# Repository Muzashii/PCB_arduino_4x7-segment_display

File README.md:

# PCB_arduino_4x7-segment_display
PCB of a module for arduino, with 4 LEDs of 7 segments for counting

# Imagens

Assembly on TinkerCad : 

Schematic of the project : 

Top layer of 3D PCB : 

Detail of the use of each pin entry : 

## Installation

##### Use KiCad to open the project file

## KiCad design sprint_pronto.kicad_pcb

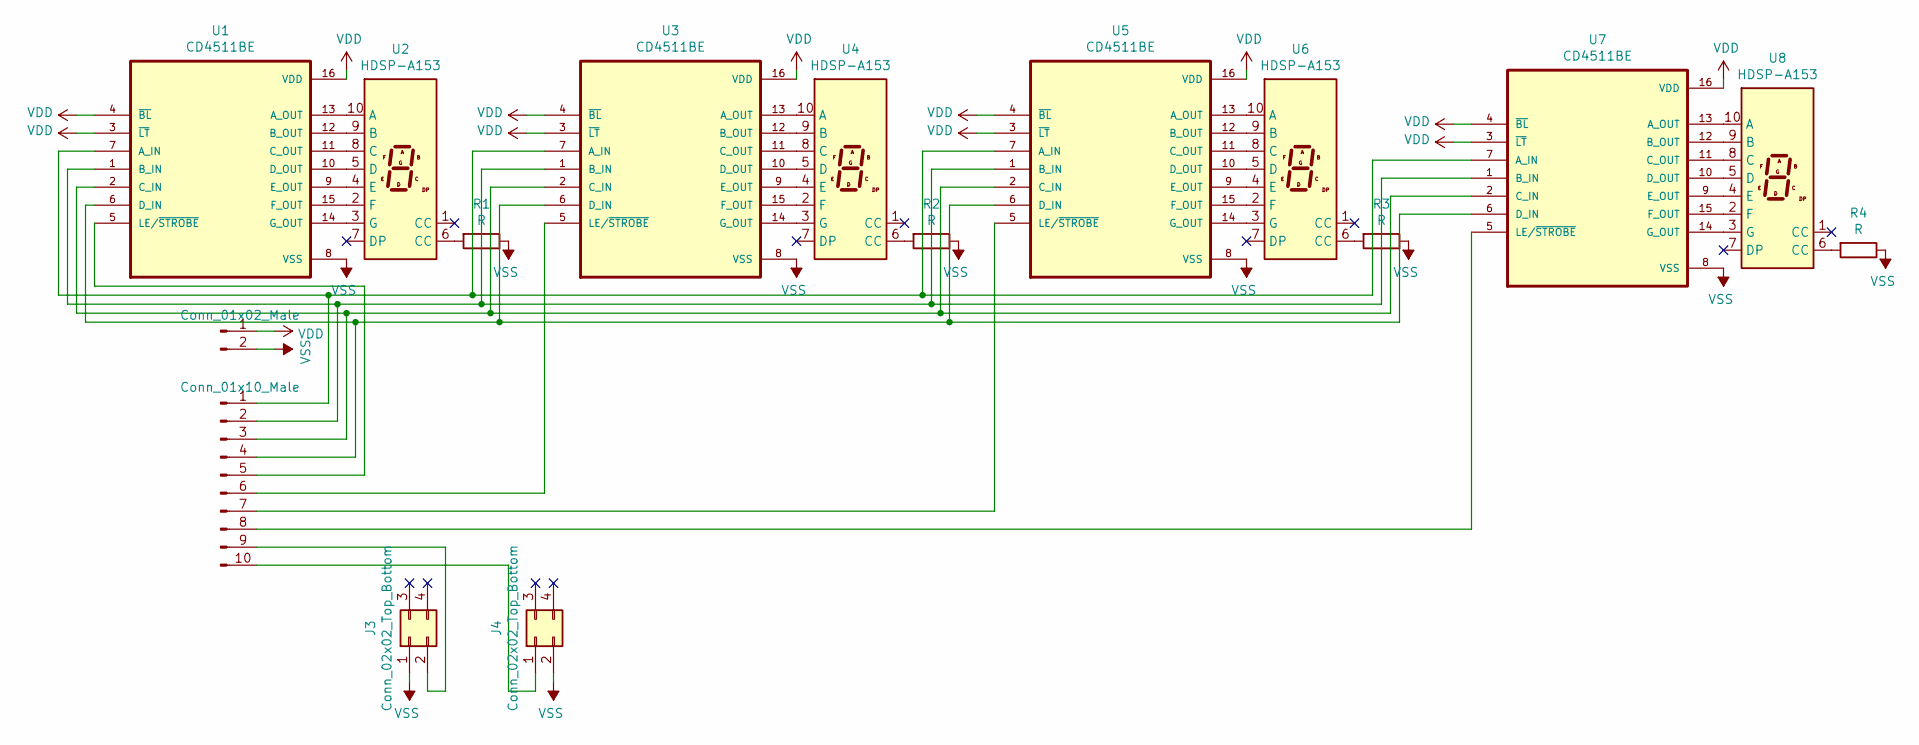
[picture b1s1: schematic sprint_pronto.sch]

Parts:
J1: Conn_01x02_Male; PinHeader_1x02_P2.54mm_Vertical
J2: Conn_01x10_Male; PinHeader_1x10_P2.54mm_Vertical
J3, J4: Conn_02x02_Top_Bottom; SW_PUSH_6mm_H5mm
R1, R2, R3, R4: R; R_Axial_DIN0207_L6.3mm_D2.5mm_P10.16mm_Horizontal
U1, U3, U5, U7: CD4511BE; DIP794W45P254L1969H508Q16
U2, U4, U6, U8: HDSP-A153; HDSP-A151

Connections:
unnamed: J2.1, U1.7 (A_IN), U3.7 (A_IN), U5.7 (A_IN), U7.7 (A_IN)
unnamed: J2.2, U1.1 (B_IN), U3.1 (B_IN), U5.1 (B_IN), U7.1 (B_IN)
unnamed: J2.3, U1.2 (C_IN), U3.2 (C_IN), U5.2 (C_IN), U7.2 (C_IN)
unnamed: J2.4, U1.6 (D_IN), U3.6 (D_IN), U5.6 (D_IN), U7.6 (D_IN)
unnamed: J2.5, U1.5 (LE/~STROBE)
unnamed: J2.6, U3.5 (LE/~STROBE)
unnamed: J2.7, U5.5 (LE/~STROBE)
unnamed: J2.8, U7.5 (LE/~STROBE)
unnamed: J2.9, J3.2
unnamed: J2.10, J4.1
unnamed: R1.2, U2.6 (CC)
unnamed: R2.2, U4.6 (CC)
unnamed: R3.2, U6.6 (CC)
unnamed: R4.2, U8.6 (CC)
unnamed: U1.9 (E_OUT), U2.4 (E)
unnamed: U1.10 (D_OUT), U2.5 (D)
unnamed: U1.11 (C_OUT), U2.8 (C)
unnamed: U1.12 (B_OUT), U2.9 (B)
unnamed: U1.13 (A_OUT), U2.10 (A)
unnamed: U1.14 (G_OUT), U2.3 (G)
unnamed: U1.15 (F_OUT), U2.2 (F)
unnamed: U3.9 (E_OUT), U4.4 (E)
unnamed: U3.10 (D_OUT), U4.5 (D)
unnamed: U3.11 (C_OUT), U4.8 (C)
unnamed: U3.12 (B_OUT), U4.9 (B)
unnamed: U3.13 (A_OUT), U4.10 (A)
unnamed: U3.14 (G_OUT), U4.3 (G)
unnamed: U3.15 (F_OUT), U4.2 (F)
unnamed: U5.9 (E_OUT), U6.4 (E)
unnamed: U5.10 (D_OUT), U6.5 (D)
unnamed: U5.11 (C_OUT), U6.8 (C)
unnamed: U5.12 (B_OUT), U6.9 (B)
unnamed: U5.13 (A_OUT), U6.10 (A)
unnamed: U5.14 (G_OUT), U6.3 (G)
unnamed: U5.15 (F_OUT), U6.2 (F)
unnamed: U7.9 (E_OUT), U8.4 (E)
unnamed: U7.10 (D_OUT), U8.5 (D)
unnamed: U7.11 (C_OUT), U8.8 (C)
unnamed: U7.12 (B_OUT), U8.9 (B)
unnamed: U7.13 (A_OUT), U8.10 (A)
unnamed: U7.14 (G_OUT), U8.3 (G)
unnamed: U7.15 (F_OUT), U8.2 (F)
VDD: J1.1, U1.3 (~LT), U1.4 (~BL), U1.16 (VDD), U3.3 (~LT), U3.4 (~BL), U3.16 (VDD), U5.3 (~LT), U5.4 (~BL), U5.16 (VDD), U7.3 (~LT), U7.4 (~BL), U7.16 (VDD)
VSS: J1.2, J3.1, J4.2, R1.1, R2.1, R3.1, R4.1, U1.8 (VSS), U3.8 (VSS), U5.8 (VSS), U7.8 (VSS)

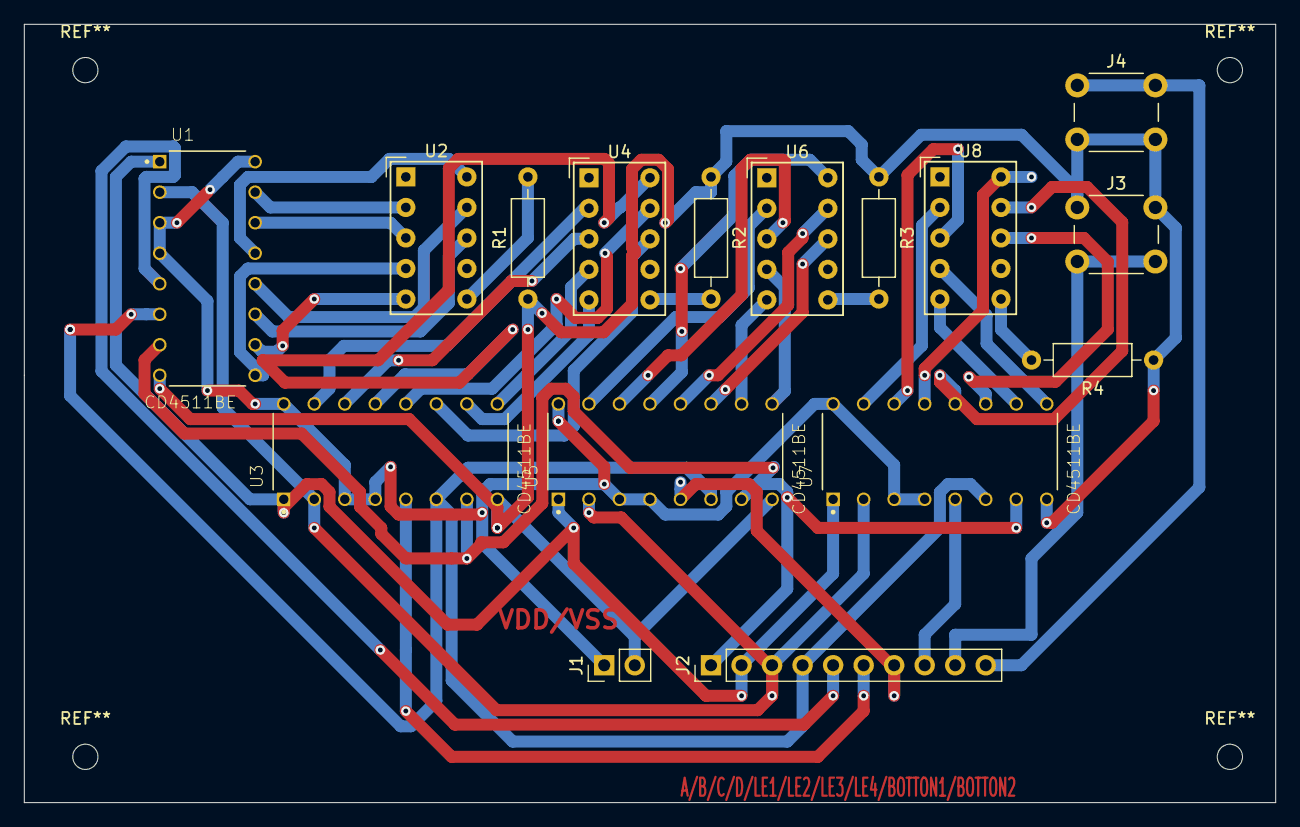
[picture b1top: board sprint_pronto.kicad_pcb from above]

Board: 2 copper layers, 104.1 x 64.8 mm, 16 parts (0 on the bottom side), 44 nets.

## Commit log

2021-05-29 FINISHED PROJECT
2021-05-31 PCB Final
